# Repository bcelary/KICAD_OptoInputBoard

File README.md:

OptoInputBoard
==============

A PCB design for Optically isolated input board based on 4n25 chip with inversion. The output can be attached to Arduino input pins or any other compatible microprocessor. Further details about this project available on:

http://racooncircuits.com/opto-isolated-input-board-arduino/

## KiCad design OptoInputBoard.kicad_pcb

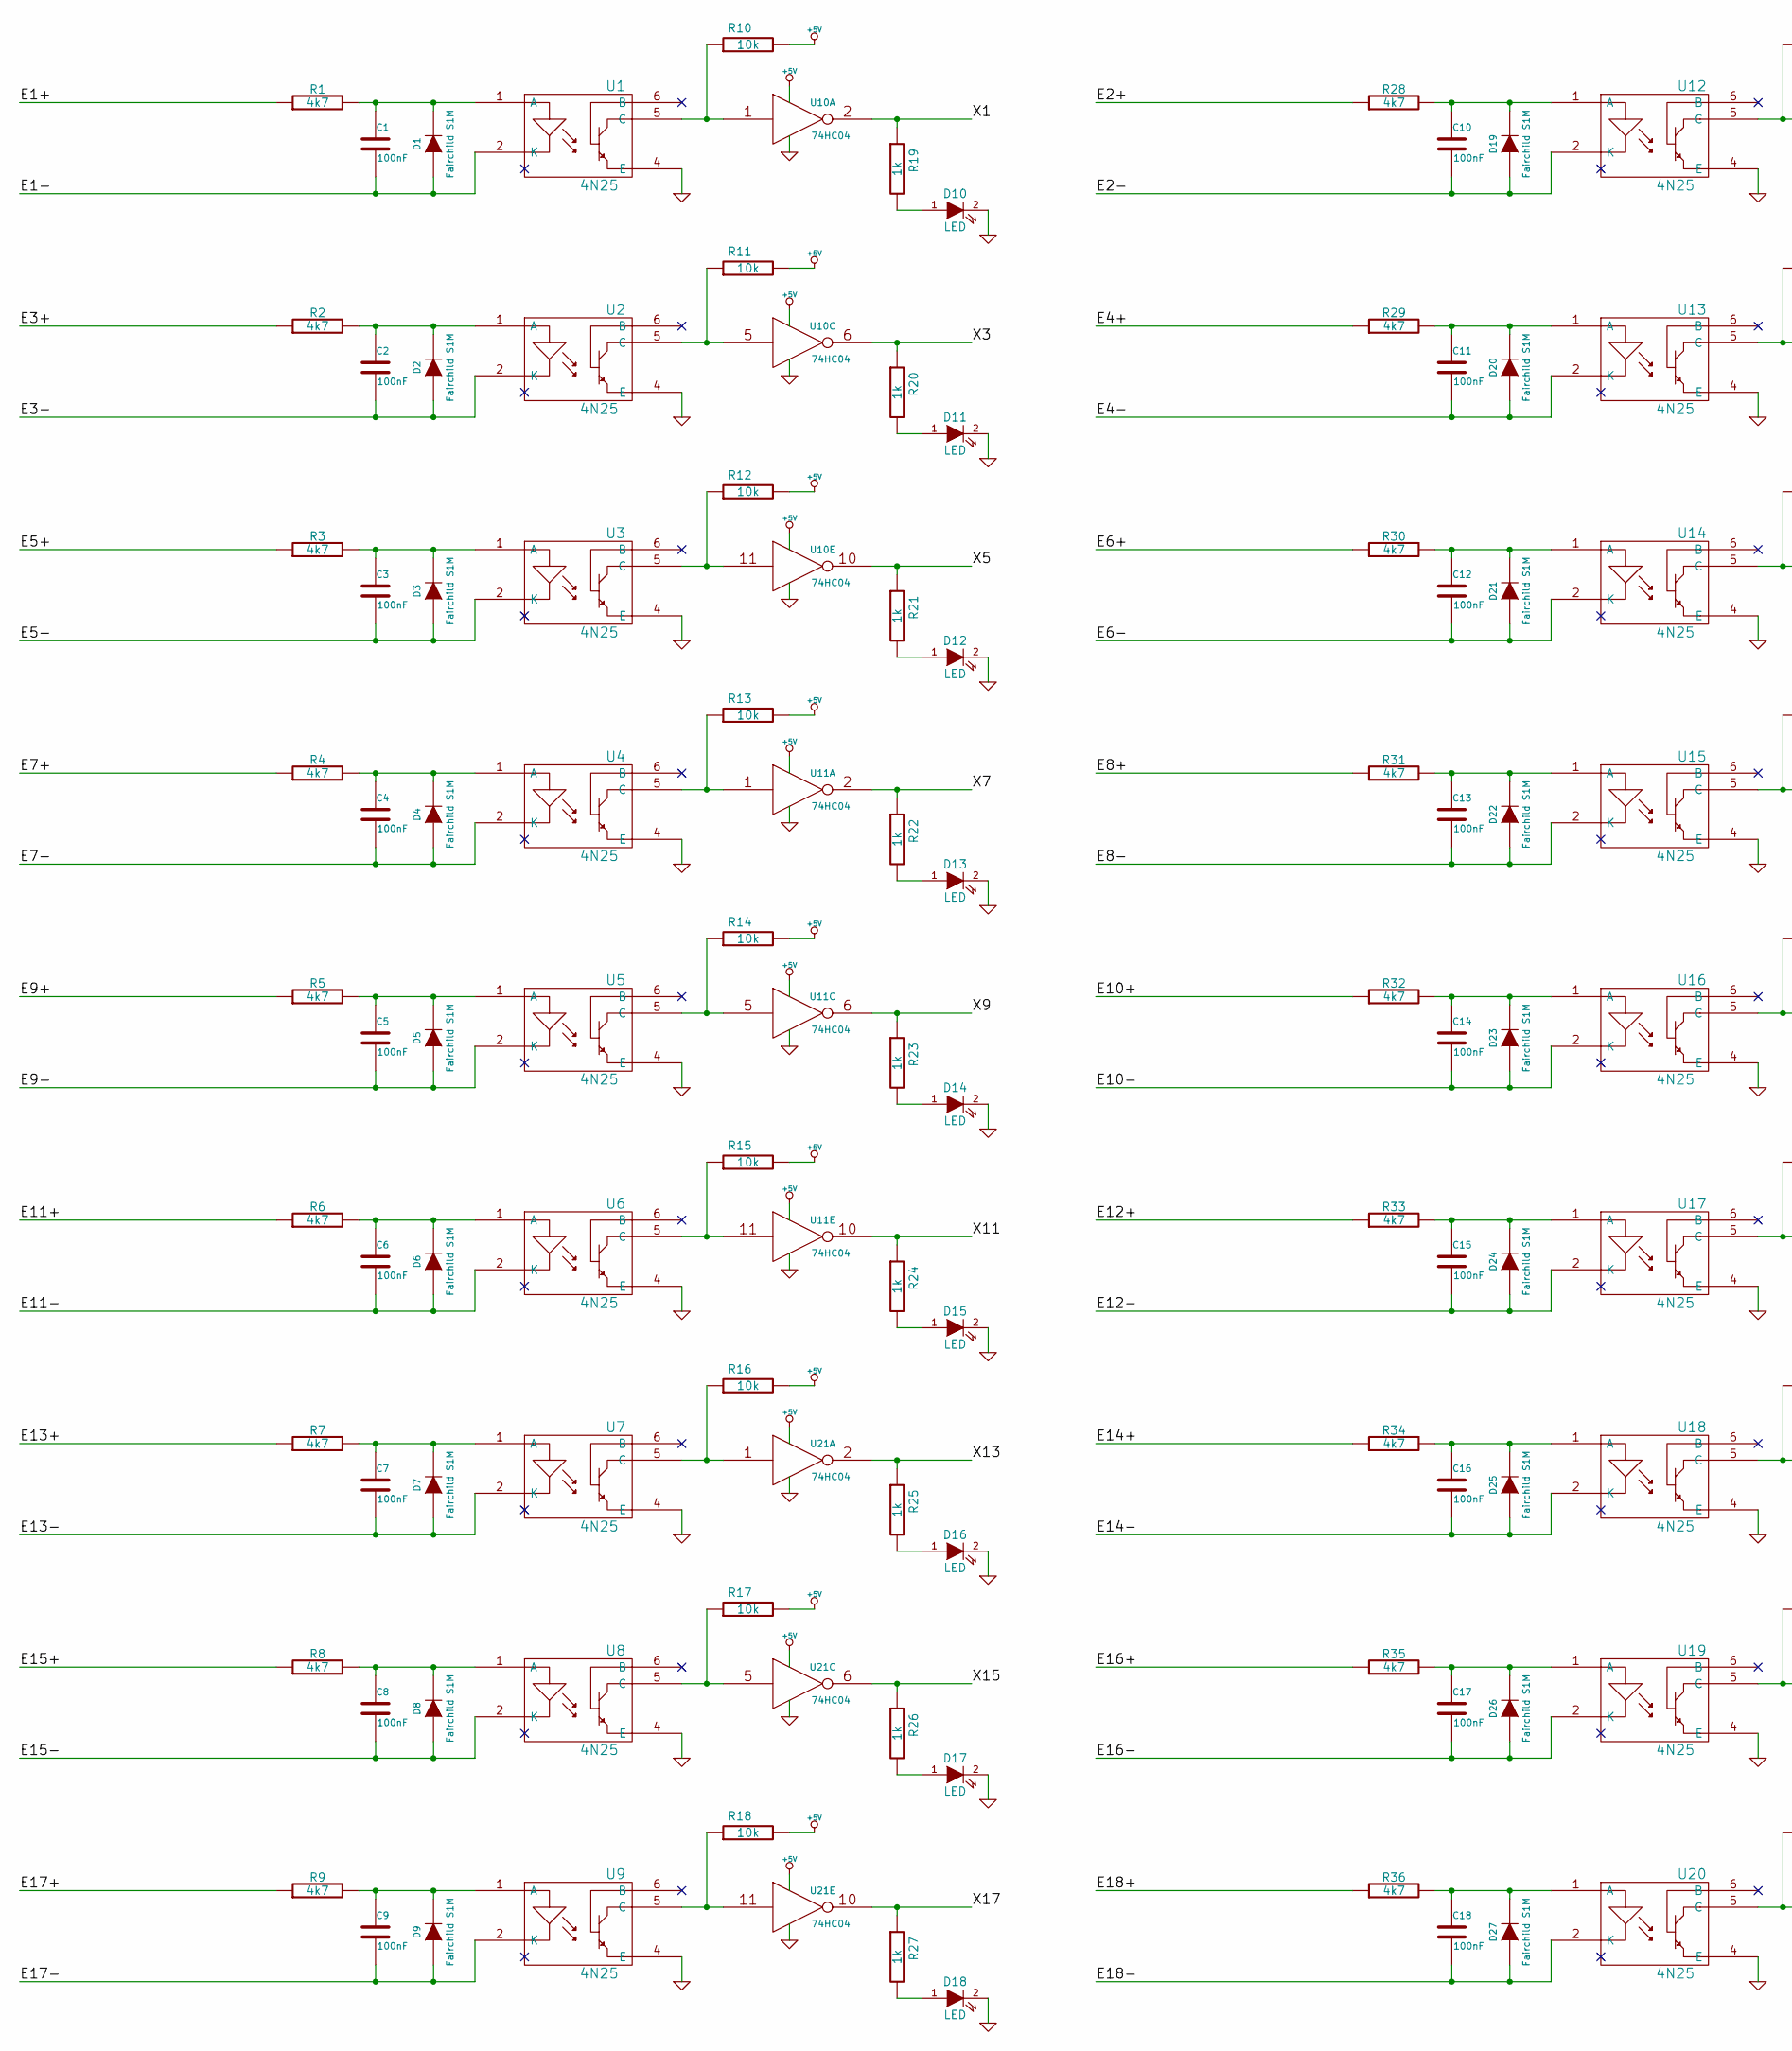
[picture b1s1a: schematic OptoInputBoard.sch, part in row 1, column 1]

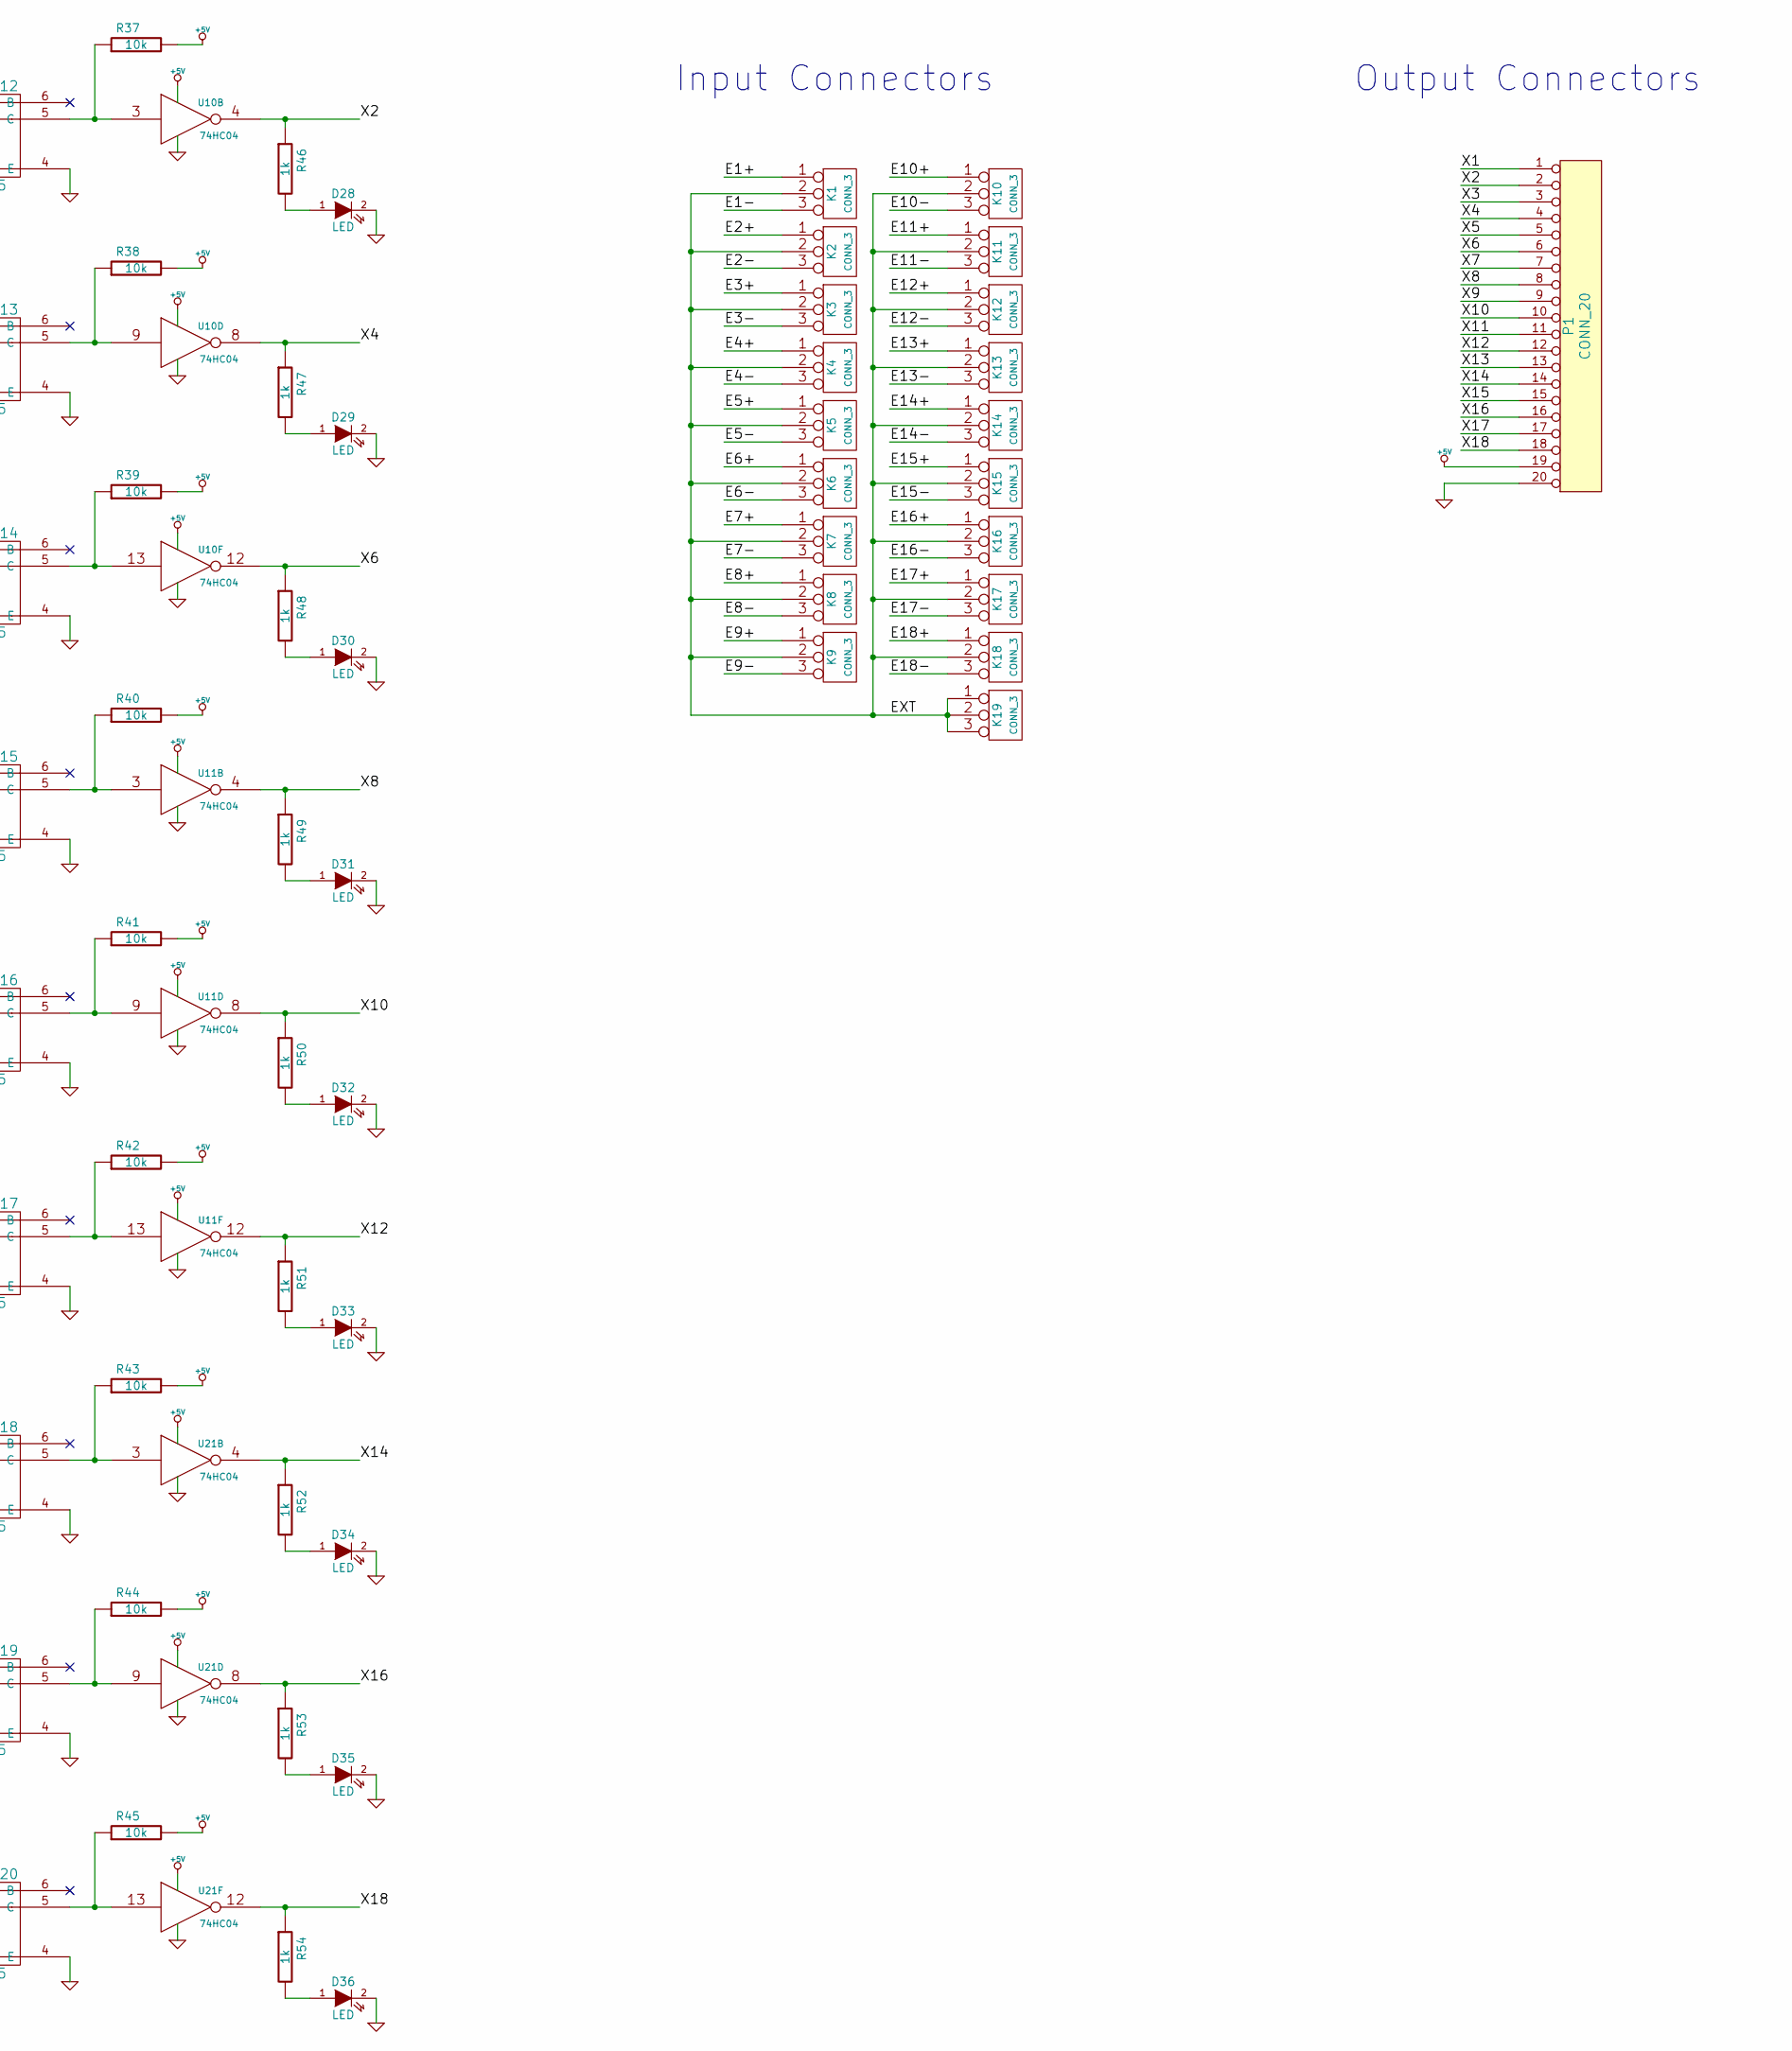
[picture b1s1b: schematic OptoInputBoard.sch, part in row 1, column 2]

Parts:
C1, C2, C3, C4, C5, C6, C7, C8, C9, C10, C11, C12, C13, C14, C15, C16, C17, C18: 100nF
D1, D2, D3, D4, D5, D6, D7, D8, D9, D19, D20, D21, D22, D23, D24, D25, D26, D27: Fairchild S1M
D10, D11, D12, D13, D14, D15, D16, D17, D18, D28, D29, D30, D31, D32, D33, D34, D35, D36: LED
K1, K2, K3, K4, K5, K6, K7, K8, K9, K10, K11, K12, K13, K14, K15, K16, K17, K18, K19: CONN_3
P1: CONN_20
R1, R2, R3, R4, R5, R6, R7, R8, R9, R28, R29, R30, R31, R32, R33, R34, R35, R36: 4k7
R10, R11, R12, R13, R14, R15, R16, R17, R18, R37, R38, R39, R40, R41, R42, R43, R44, R45: 10k
R19, R20, R21, R22, R23, R24, R25, R26, R27, R46, R47, R48, R49, R50, R51, R52, R53, R54: 1k
U1, U2, U3, U4, U5, U6, U7, U8, U9, U12, U13, U14, U15, U16, U17, U18, U19, U20: 4N25
U10, U11, U21: 74HC04

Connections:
+5V: P1.19, R10.2, R11.2, R12.2, R13.2, R14.2, R15.2, R16.2, R17.2, R18.2, R37.2, R38.2, R39.2, R40.2, R41.2, R42.2, R43.2, R44.2, R45.2, U10.14 (VCC), U11.14 (VCC), U21.14 (VCC)
/E1+: K1.1, R1.1
/E1-: C1.2, D1.1 (A), K1.3, U1.2 (K)
/E2+: K2.1, R28.1
/E2-: C10.2, D19.1 (A), K2.3, U12.2 (K)
/E3+: K3.1, R2.1
/E3-: C2.2, D2.1 (A), K3.3, U2.2 (K)
/E4+: K4.1, R29.1
/E4-: C11.2, D20.1 (A), K4.3, U13.2 (K)
/E5+: K5.1, R3.1
/E5-: C3.2, D3.1 (A), K5.3, U3.2 (K)
/E6+: K6.1, R30.1
/E6-: C12.2, D21.1 (A), K6.3, U14.2 (K)
/E7+: K7.1, R4.1
/E7-: C4.2, D4.1 (A), K7.3, U4.2 (K)
/E8+: K8.1, R31.1
/E8-: C13.2, D22.1 (A), K8.3, U15.2 (K)
/E9+: K9.1, R5.1
/E9-: C5.2, D5.1 (A), K9.3, U5.2 (K)
/E10+: K10.1, R32.1
/E10-: C14.2, D23.1 (A), K10.3, U16.2 (K)
/E11+: K11.1, R6.1
/E11-: C6.2, D6.1 (A), K11.3, U6.2 (K)
/E12+: K12.1, R33.1
/E12-: C15.2, D24.1 (A), K12.3, U17.2 (K)
/E13+: K13.1, R7.1
/E13-: C7.2, D7.1 (A), K13.3, U7.2 (K)
/E14+: K14.1, R34.1
/E14-: C16.2, D25.1 (A), K14.3, U18.2 (K)
/E15+: K15.1, R8.1
/E15-: C8.2, D8.1 (A), K15.3, U8.2 (K)
/E16+: K16.1, R35.1
/E16-: C17.2, D26.1 (A), K16.3, U19.2 (K)
/E17+: K17.1, R9.1
/E17-: C9.2, D9.1 (A), K17.3, U9.2 (K)
/E18+: K18.1, R36.1
/E18-: C18.2, D27.1 (A), K18.3, U20.2 (K)
/EXT: K1.2 (PM), K2.2 (PM), K3.2 (PM), K4.2 (PM), K5.2 (PM), K6.2 (PM), K7.2 (PM), K8.2 (PM), K9.2 (PM), K10.2 (PM), K11.2 (PM), K12.2 (PM), K13.2 (PM), K14.2 (PM), K15.2 (PM), K16.2 (PM), K17.2 (PM), K18.2 (PM), K19.1, K19.2 (PM), K19.3
/X1: P1.1, R19.1, U10.2
/X2: P1.2, R46.1, U10.4
/X3: P1.3, R20.1, U10.6
/X4: P1.4, R47.1, U10.8
/X5: P1.5, R21.1, U10.10
/X6: P1.6, R48.1, U10.12
/X7: P1.7, R22.1, U11.2
/X8: P1.8, R49.1, U11.4
/X9: P1.9, R23.1, U11.6
/X10: P1.10, R50.1, U11.8
/X11: P1.11, R24.1, U11.10
/X12: P1.12, R51.1, U11.12
/X13: P1.13, R25.1, U21.2
/X14: P1.14, R52.1, U21.4
/X15: P1.15, R26.1, U21.6
/X16: P1.16, R53.1, U21.8
/X17: P1.17, R27.1, U21.10
/X18: P1.18, R54.1, U21.12
GND: D10.2 (K), D11.2 (K), D12.2 (K), D13.2 (K), D14.2 (K), D15.2 (K), D16.2 (K), D17.2 (K), D18.2 (K), D28.2 (K), D29.2 (K), D30.2 (K), D31.2 (K), D32.2 (K), D33.2 (K), D34.2 (K), D35.2 (K), D36.2 (K), P1.20, U1.4 (E), U2.4 (E), U3.4 (E), U4.4 (E), U5.4 (E), U6.4 (E), U7.4 (E), U8.4 (E), U9.4 (E), U10.7 (GND), U11.7 (GND), U12.4 (E), U13.4 (E), U14.4 (E), U15.4 (E), U16.4 (E), U17.4 (E), U18.4 (E), U19.4 (E), U20.4 (E), U21.7 (GND)
unnamed: C1.1, D1.2 (K), R1.2, U1.1 (A)
unnamed: C2.1, D2.2 (K), R2.2, U2.1 (A)
unnamed: C3.1, D3.2 (K), R3.2, U3.1 (A)
unnamed: C4.1, D4.2 (K), R4.2, U4.1 (A)
unnamed: C5.1, D5.2 (K), R5.2, U5.1 (A)
unnamed: C6.1, D6.2 (K), R6.2, U6.1 (A)
unnamed: C7.1, D7.2 (K), R7.2, U7.1 (A)
unnamed: C8.1, D8.2 (K), R8.2, U8.1 (A)
unnamed: C9.1, D9.2 (K), R9.2, U9.1 (A)
unnamed: C10.1, D19.2 (K), R28.2, U12.1 (A)
unnamed: C11.1, D20.2 (K), R29.2, U13.1 (A)
unnamed: C12.1, D21.2 (K), R30.2, U14.1 (A)
unnamed: C13.1, D22.2 (K), R31.2, U15.1 (A)
unnamed: C14.1, D23.2 (K), R32.2, U16.1 (A)
unnamed: C15.1, D24.2 (K), R33.2, U17.1 (A)
unnamed: C16.1, D25.2 (K), R34.2, U18.1 (A)
unnamed: C17.1, D26.2 (K), R35.2, U19.1 (A)
unnamed: C18.1, D27.2 (K), R36.2, U20.1 (A)
unnamed: D10.1 (A), R19.2
unnamed: D11.1 (A), R20.2
unnamed: D12.1 (A), R21.2
unnamed: D13.1 (A), R22.2
unnamed: D14.1 (A), R23.2
unnamed: D15.1 (A), R24.2
unnamed: D16.1 (A), R25.2
unnamed: D17.1 (A), R26.2
unnamed: D18.1 (A), R27.2
unnamed: D28.1 (A), R46.2
unnamed: D29.1 (A), R47.2
unnamed: D30.1 (A), R48.2
unnamed: D31.1 (A), R49.2
unnamed: D32.1 (A), R50.2
unnamed: D33.1 (A), R51.2
unnamed: D34.1 (A), R52.2
unnamed: D35.1 (A), R53.2
unnamed: D36.1 (A), R54.2
unnamed: R10.1, U1.5 (C), U10.1
unnamed: R11.1, U2.5 (C), U10.5
unnamed: R12.1, U3.5 (C), U10.11
unnamed: R13.1, U4.5 (C), U11.1
unnamed: R14.1, U5.5 (C), U11.5
unnamed: R15.1, U6.5 (C), U11.11
unnamed: R16.1, U7.5 (C), U21.1
unnamed: R17.1, U8.5 (C), U21.5
unnamed: R18.1, U9.5 (C), U21.11
unnamed: R37.1, U10.3, U12.5 (C)
unnamed: R38.1, U10.9, U13.5 (C)
unnamed: R39.1, U10.13, U14.5 (C)
unnamed: R40.1, U11.3, U15.5 (C)
unnamed: R41.1, U11.9, U16.5 (C)
unnamed: R42.1, U11.13, U17.5 (C)
unnamed: R43.1, U18.5 (C), U21.3
unnamed: R44.1, U19.5 (C), U21.9
unnamed: R45.1, U20.5 (C), U21.13

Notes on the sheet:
Input Connectors
Output Connectors

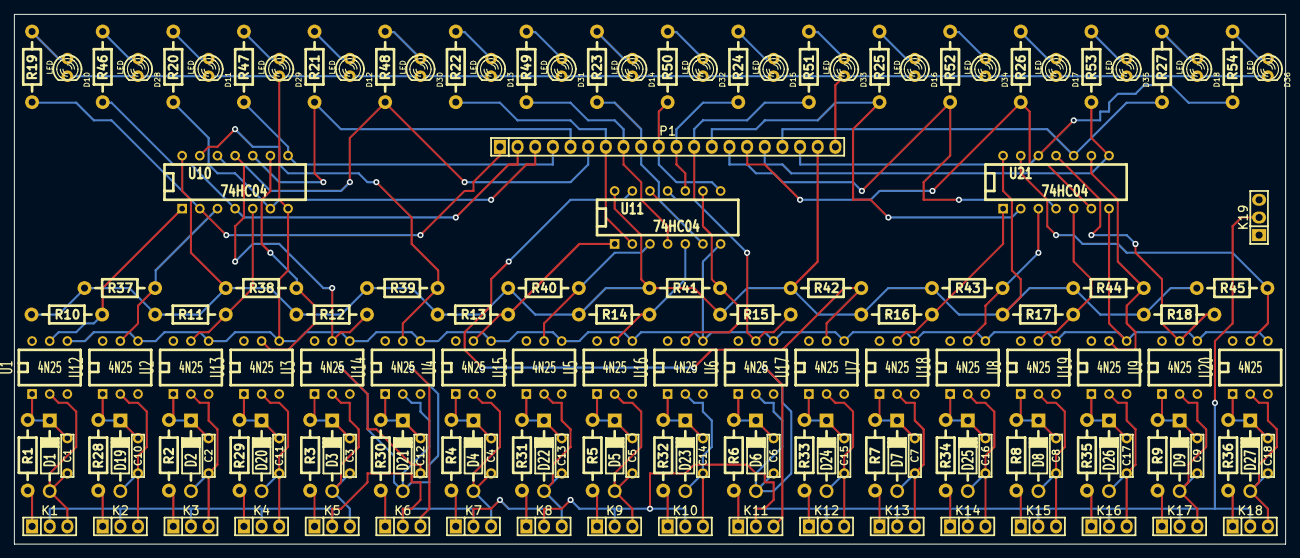
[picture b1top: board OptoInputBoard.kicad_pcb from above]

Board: 2 copper layers, 182.9 x 76.2 mm, 149 parts (0 on the bottom side), 111 nets.

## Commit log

2014-12-12 saved with new kicad version
